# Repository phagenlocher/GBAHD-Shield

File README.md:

# gbaHD Shield
This is a shield for the [gbaHD project](https://github.com/zwenergy/gbaHD).  

This particular fork does change certain parts, but does not add any new features.

#### Features:
- Connects via female headers to the Edge board (shield)
- Has a FFC 40 pin connector for OGBA LCD connector. Need Type-B Cable (Reverse) vvv=======^^^
- Has a FFC 32 pin connector for OGBA LCD connector. Need Type-B Cable (Reverse) vvv=======^^^
- Has a FFC 34 pin connector for GBA-SP LCD connector. Need Type-A Cable (Direct) vvv=======vvv
- Has a FFC 16 pin connector for controls with a wire up board. Need Type-B Cable (Reverse) vvv=======^^^
- Has a ATMEGA328p for using a SNES connector to control the GBA.
- Has a high-side switch for GBA power controls (IGR).
- Has eight (8) testpoints on the bottom side for future features.

## Issues
- no known issues

## Contributing
If you wish to contribute, see something wrong or want to add a feature please make a pull request or leave an issue!

## BOM
|Reference	|Value							|
|---------	|--------						|
|C1, C3		|100nF 0805						|
|C2			|22uF 0805						|
|R1			|2.2K 0805						|
|R2			|1K 0805						|
|R3, R4		|10K 0805						|
|U1			|AMS1117-ADJ SOT223-3			|
|U2,U3		|74HC595 SOIC-16				|
|U4			|SNES 7Pin						|
|U5			|ATMEGA328p-AU					|
|SW1		|Push Button THT 6mm			|
|J2			|JUSHUO AFC07-S32FCC-00			|
|J3			|JUSHUO AFC07-S34FCC-00			|
|J4			|JUSHUO_AFC07-S16FCC-00			|
|J5			|JUSHUO AFC07-S40FCC-00			|
|J6			|PinHeader 1x6 2.54mm			|
|J7, J9		|PinHeader 1x8 2.54mm			|
|J8, J10	|PinHeader 1x10 2.54mm			|
|J11		|PinHeader 2x03 2.54mm			|
|Q1			|SI2301DS P-Chan MOSFET	SOT23	|

## Programming the MCU
In order to program the MCU, you need an arduino to use as ISP.  
Use the following image to wire up an arduino to the board to program it.  
**I would also recomend programming while it's not seated in the FPGA board.**
  
After wiring the board, follow this tutorial to flash the the sketch to the board.  
[ICSP Tutorial](https://www.arduino.cc/en/pmwiki.php?n=Tutorial/ArduinoISP)
As target board choose "Arduino Pro or Pro Mini -  ATmega328p - 8MHz"
Fuses must be Low: 0xE2 High: 0xD9 Ext: 0xFF

## Choosing the supply voltage
As the OGBA and the GBA-SP use different battery technologies, they also require different voltages.
The OGBA needs approx. 3V (2x 1.5V from AA cells - 3.3 will also fit) and the GBA-SP needs 3.3 - 4.2V (Lithium battery - 4.0V will also fit).
Therefore we have a solder-jumper (JP1) which we use to choose between 3.3V and 4.0V.
Plus we need to solder-bridge J1 and J12 due to the fact, that the power-managing chip on the SP mainboard blocks the power on if it detected a
low battery recently. This will replace the power switch which therefore needs to be in **off position always!** 
**v20210406 Owners** If you want to use this board with an SP simply connect the J1 to the VCC-line on the shield and on the mainboard connect EX1 with BAT+ and VCC with VCC.

## Images

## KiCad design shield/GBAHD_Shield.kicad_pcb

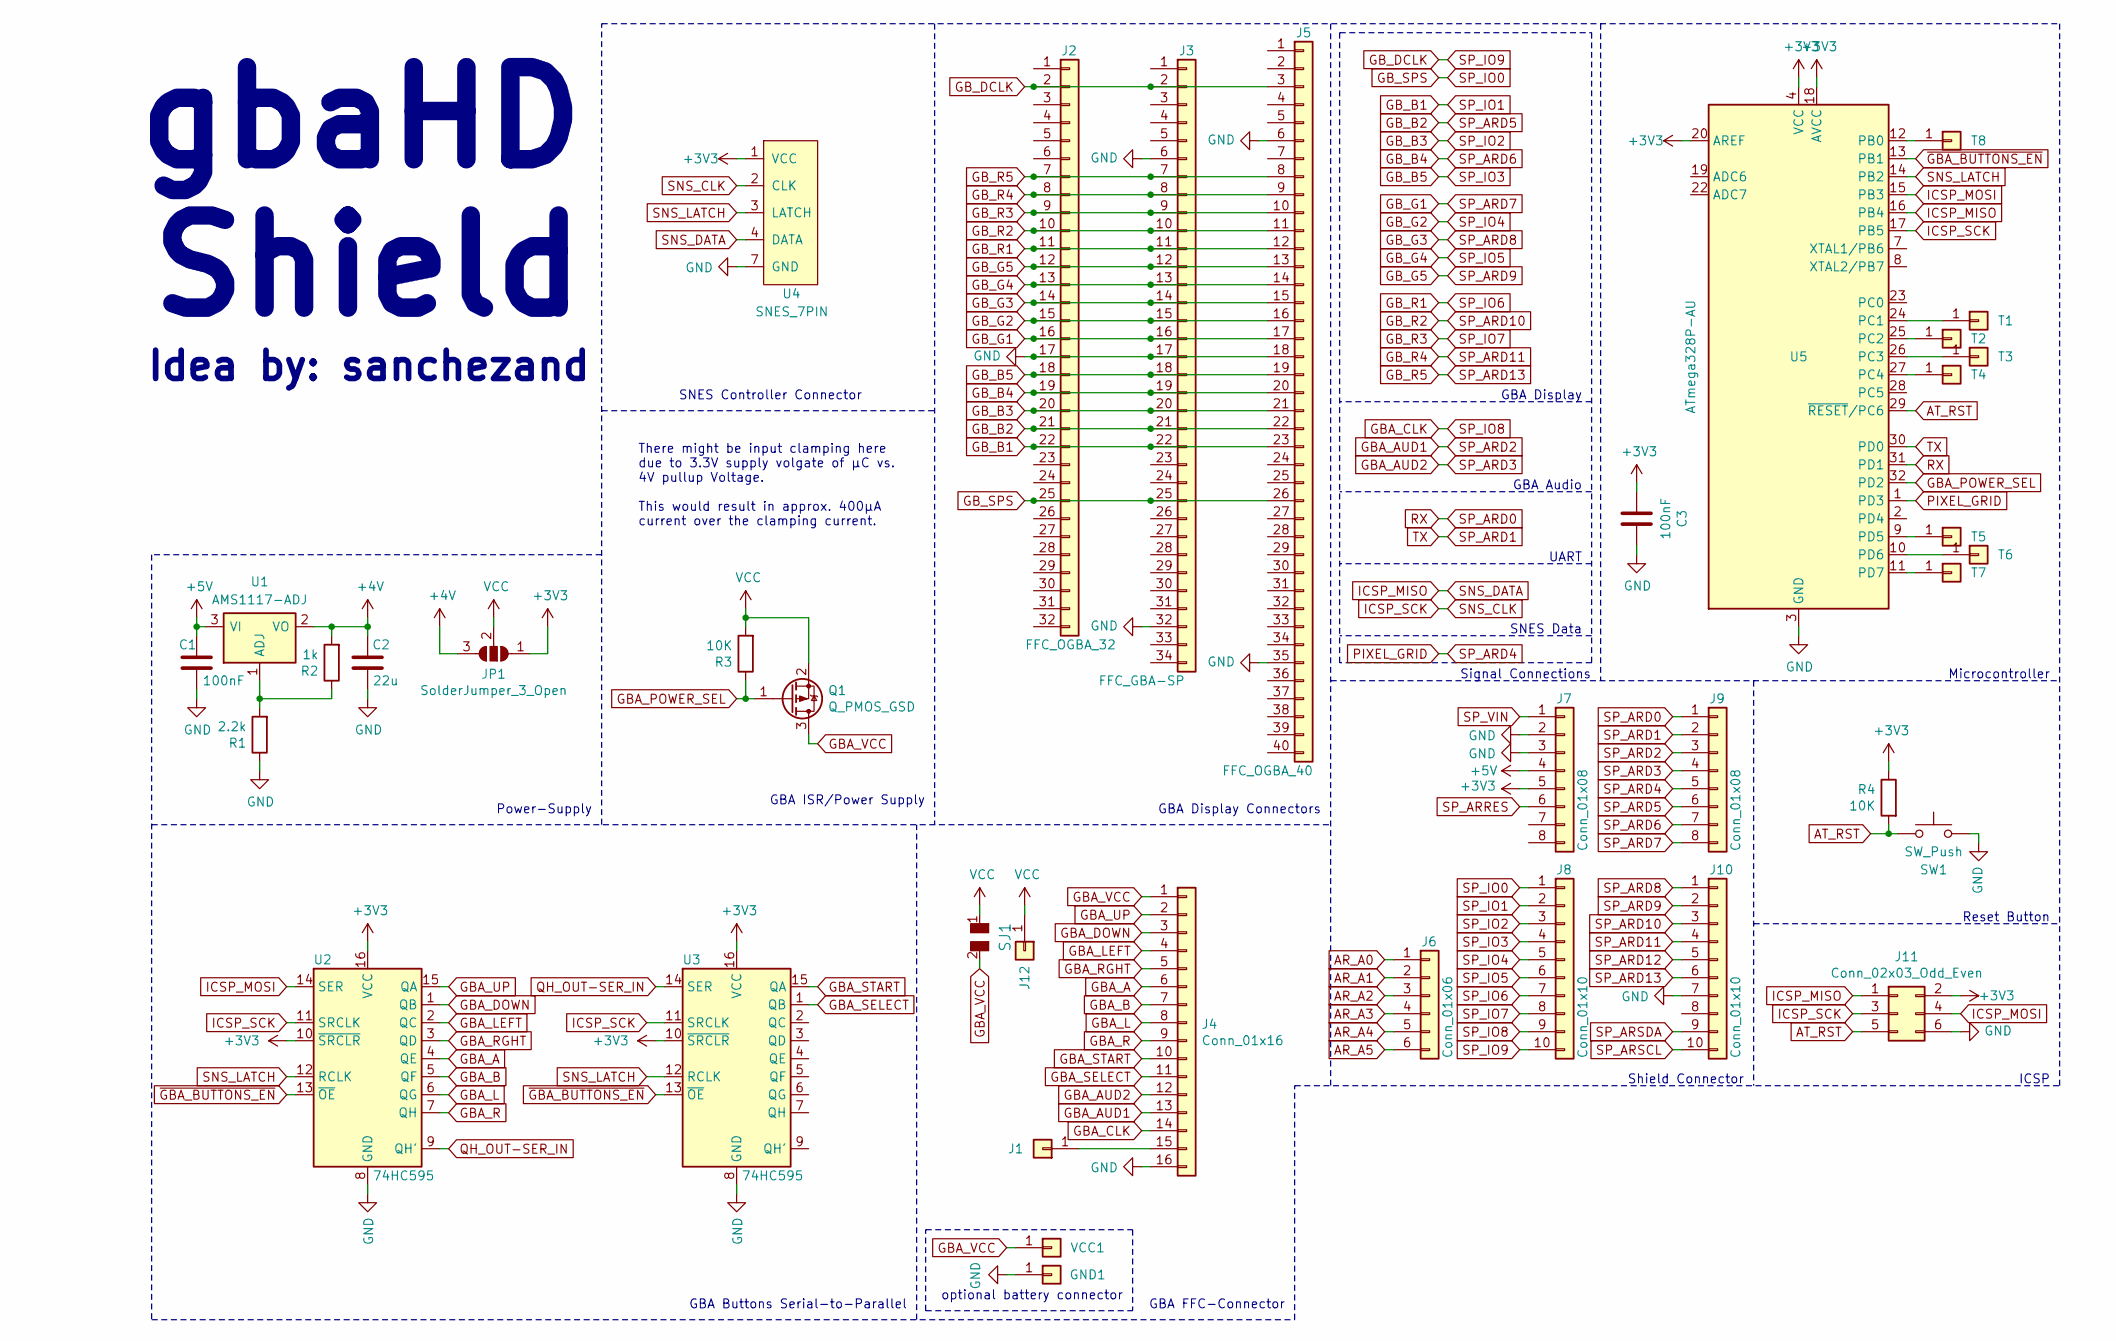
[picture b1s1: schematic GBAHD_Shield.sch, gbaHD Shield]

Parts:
C1, C3: 100nF; C_0805_2012Metric_Pad1.18x1.45mm_HandSolder
C2: 22u; C_0805_2012Metric_Pad1.18x1.45mm_HandSolder
GND1: Conn_01x01; TestPoint_Pad_1.5x1.5mm
J1, J12: Conn_01x01; TestPoint_Pad_1.5x1.5mm
J2: FFC_OGBA_32; TE_3-1734839-2_1x32-1MP_P0.5mm_Horizontal
J3: FFC_GBA-SP; TE_3-1734839-4_1x34-1MP_P0.5mm_Horizontal
J4: Conn_01x16; TE_1-1734839-6_1x16-1MP_P0.5mm_Horizontal
J5: FFC_OGBA_40; TE_4-1734839-0_1x40-1MP_P0.5mm_Horizontal
J6: Conn_01x06; PinHeader_1x06_P2.54mm_Vertical
J7, J9: Conn_01x08; PinHeader_1x08_P2.54mm_Vertical
J8, J10: Conn_01x10; PinHeader_1x10_P2.54mm_Vertical
J11: Conn_02x03_Odd_Even; PinHeader_2x03_P2.54mm_Vertical
JP1: SolderJumper_3_Open; SolderJumper-3_P1.3mm_Open_Pad1.0x1.5mm_NumberLabels
Q1: Q_PMOS_GSD; SOT-23
R1: 2.2k; R_0805_2012Metric_Pad1.20x1.40mm_HandSolder
R2: 1k; R_0805_2012Metric_Pad1.20x1.40mm_HandSolder
R3, R4: 10K; R_0805_2012Metric_Pad1.20x1.40mm_HandSolder
SJ1: SOLDER_JUMPER; SolderJumper-2_P1.3mm_Open_TrianglePad1.0x1.5mm
SW1: SW_Push; SW_PUSH_6mm
T1, T2, T3, T4, T5, T6, T7, T8: Conn_01x01; TestPoint_Pad_1.5x1.5mm
U1: AMS1117-ADJ; SOT-223-3_TabPin2
U2, U3: 74HC595; SOIC-16_3.9x9.9mm_P1.27mm
U4: SNES_7PIN
U5: ATmega328P-AU; TQFP-32_7x7mm_P0.8mm
VCC1: Conn_01x01; TestPoint_Pad_1.5x1.5mm

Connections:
+3V3: C3.2, J7.5, J11.2, JP1.1 (A), R4.1, U2.10 (~SRCLR), U2.16 (VCC), U3.10 (~SRCLR), U3.16 (VCC), U4.1 (VCC), U5.4 (VCC), U5.6 (VCC), U5.18 (AVCC), U5.20 (AREF)
+4V: C2.2, JP1.3 (B), R2.2, U1.2 (VO)
+5V: C1.2, J7.4, U1.3 (VI)
AR_A0: J6.1
AR_A1: J6.2
AR_A2: J6.3
AR_A3: J6.4
AR_A4: J6.5
AR_A5: J6.6
AT_RST: J11.5, R4.2, SW1.1, U5.29 (~RESET~/PC6)
GBA_A: J4.6, U2.4 (QE)
GBA_AUD1: J4.13, J9.3
GBA_AUD2: J4.12, J9.4
GBA_B: J4.7, U2.5 (QF)
GBA_CLK: J4.14, J8.9
GBA_DOWN: J4.3, U2.1 (QB)
GBA_L: J4.8, U2.6 (QG)
GBA_LEFT: J4.4, U2.2 (QC)
GBA_POWER_SEL: Q1.1 (G), R3.1, U5.32 (PD2)
GBA_R: J4.9, U2.7 (QH)
GBA_RGHT: J4.5, U2.3 (QD)
GBA_SELECT: J4.11, U3.1 (QB)
GBA_START: J4.10, U3.15 (QA)
GBA_UP: J4.2, U2.15 (QA)
GBA_VCC: J4.1, Q1.3 (D), SJ1.2, VCC1.1
GB_B1: J2.22, J3.22, J5.23, J8.2
GB_B2: J2.21, J3.21, J5.22, J9.6
GB_B3: J2.20, J3.20, J5.21, J8.3
GB_B4: J2.19, J3.19, J5.20, J9.7
GB_B5: J2.18, J3.18, J5.19, J8.4
GB_DCLK: J2.2, J3.2, J5.3, J8.10
GB_G1: J2.16, J3.16, J5.17, J9.8
GB_G2: J2.15, J3.15, J5.16, J8.5
GB_G3: J2.14, J3.14, J5.15, J10.1
GB_G4: J2.13, J3.13, J5.14, J8.6
GB_G5: J2.12, J3.12, J5.13, J10.2
GB_R1: J2.11, J3.11, J5.12, J8.7
GB_R2: J2.10, J3.10, J5.11, J10.3
GB_R3: J2.9, J3.9, J5.10, J8.8
GB_R4: J2.8, J3.8, J5.9, J10.4
GB_R5: J2.7, J3.7, J5.8, J10.6
GB_SPS: J2.25, J3.25, J5.26, J8.1
GND: C1.1, C2.1, C3.1, GND1.1, J2.17, J3.6, J3.17, J3.32, J4.16, J5.6, J5.18, J5.35, J7.2, J7.3, J10.7, J11.6, R1.1, SW1.2, U2.8 (GND), U3.8 (GND), U4.7 (GND), U5.3 (GND), U5.5 (GND), U5.21 (GND)
ICSP_MISO: J11.1, U4.4 (DATA), U5.16 (PB4)
ICSP_MOSI: J11.4, U2.14 (SER), U5.15 (PB3)
ICSP_SCK: J11.3, U2.11 (SRCLK), U3.11 (SRCLK), U4.2 (CLK), U5.17 (PB5)
unnamed: J1.1, J4.15
unnamed: R1.2, R2.1, U1.1 (ADJ)
unnamed: T1.1, U5.24 (PC1)
unnamed: T2.1, U5.25 (PC2)
unnamed: T3.1, U5.26 (PC3)
unnamed: T4.1, U5.27 (PC4)
unnamed: T5.1, U5.9 (PD5)
unnamed: T6.1, U5.10 (PD6)
unnamed: T7.1, U5.11 (PD7)
unnamed: T8.1, U5.12 (PB0)
PIXEL_GRID: J9.5, U5.1 (PD3)
QH_OUT-SER_IN: U2.9 (QH'), U3.14 (SER)
RX: J9.1, U5.31 (PD1)
SNS_LATCH: U2.12 (RCLK), U3.12 (RCLK), U4.3 (LATCH), U5.14 (PB2)
SP_ARD1: J9.2, U5.30 (PD0)
SP_ARD12: J10.5
SP_ARRES: J7.6
SP_ARSCL: J10.10
SP_ARSDA: J10.9
SP_VIN: J7.1
VCC: J12.1, JP1.2 (C), Q1.2 (S), R3.2, SJ1.1
~GBA_BUTTONS_EN~: U2.13 (~OE), U3.13 (~OE), U5.13 (PB1)

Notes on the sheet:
ICSP
Reset Button
Microcontroller
Shield Connector
Signal Connections
SNES Data
UART
GBA Display
GBA Audio
GBA Display Connectors
GBA FFC-Connector
GBA Buttons Serial-to-Parallel
SNES Controller Connector
GBA ISR/Power Supply
gbaHD Shield
Idea by: sanchezand
Power-Supply
optional battery connector
There might be input clamping here due to 3.3V supply volgate of µC vs. 4V pullup Voltage. This would result in approx. 400µA current over the clamping current.

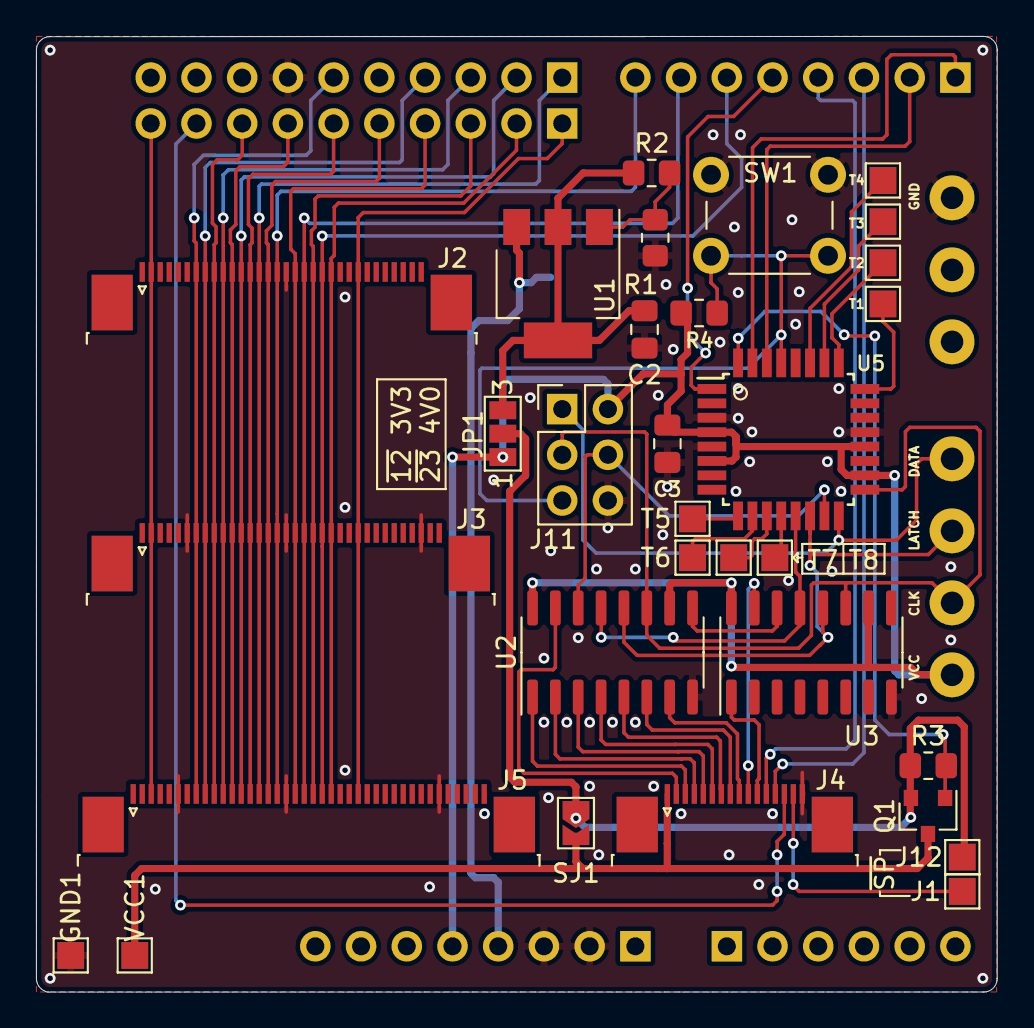
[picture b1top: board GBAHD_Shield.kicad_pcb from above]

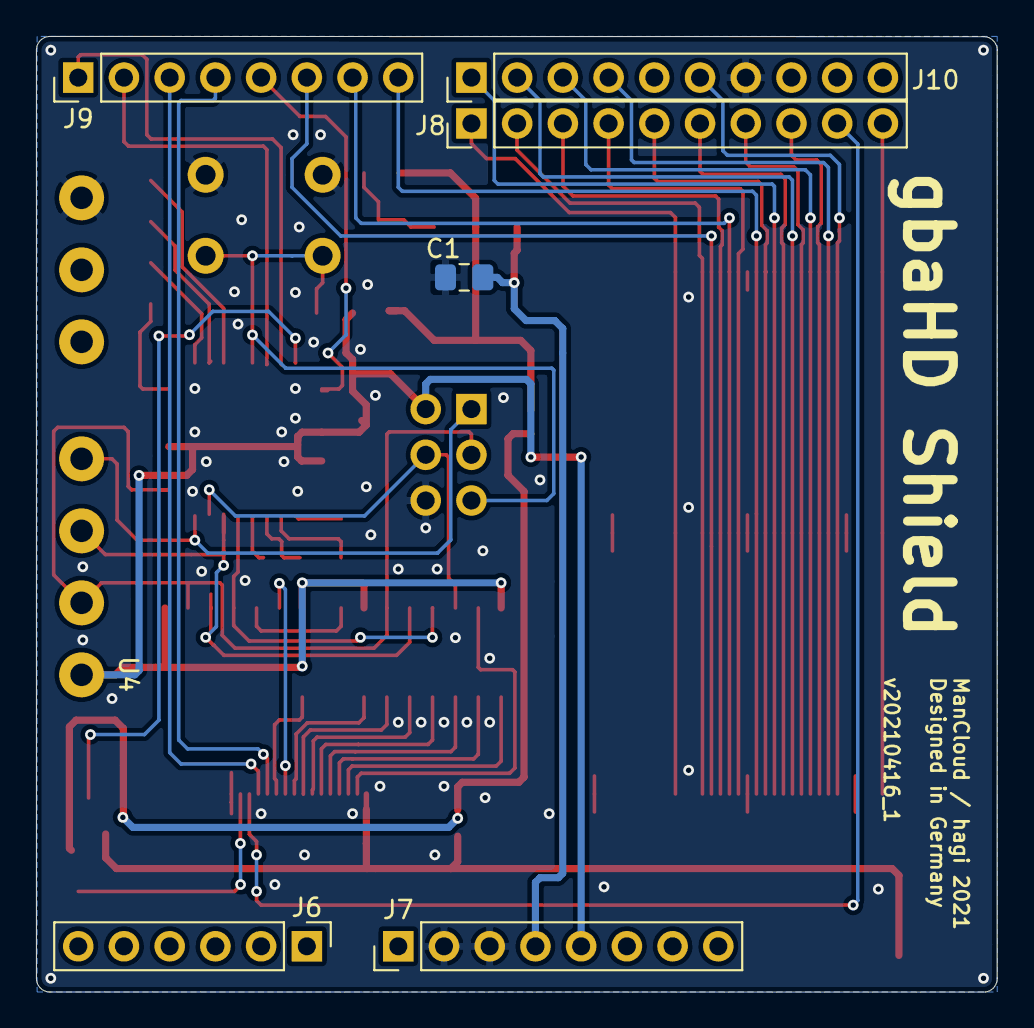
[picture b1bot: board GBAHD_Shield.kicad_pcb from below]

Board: 2 copper layers, 53.4 x 53.1 mm, 38 parts (7 on the bottom side), 57 nets.

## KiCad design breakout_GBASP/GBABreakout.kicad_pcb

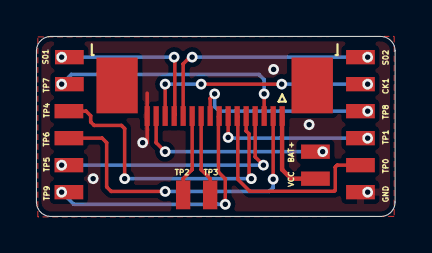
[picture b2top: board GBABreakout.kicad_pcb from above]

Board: 2 copper layers, 19.9 x 10.0 mm, 17 parts (0 on the bottom side), 16 nets.

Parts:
J1: Conn_01x16; TE_1-1734839-6_1x16-1MP_P0.5mm_Horizontal
J2: VCC; SOLDER_PAD
J3: TP6; SOLDER_PAD
J4: TP7; SOLDER_PAD
J5: TP5; SOLDER_PAD
J6: TP4; SOLDER_PAD
J7: TP0; SOLDER_PAD
J8: TP1; SOLDER_PAD
J9: TP9; SOLDER_PAD
J10: TP8; SOLDER_PAD
J11: TP3; SOLDER_PAD
J12: TP2; SOLDER_PAD
J13: S02; SOLDER_PAD
J14: S01; SOLDER_PAD
J15: CK1; SOLDER_PAD
J16: BAT+; SOLDER_PAD
J17: GND; SOLDER_PAD

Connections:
BAT+: J1.15, J16.1
GBA_A: J1.6, J7.1
GBA_AUD1: J1.13, J14.1
GBA_AUD2: J1.12, J13.1
GBA_B: J1.7, J8.1
GBA_CLK: J1.14, J15.1
GBA_DOWN: J1.3, J4.1
GBA_L: J1.8, J9.1
GBA_LEFT: J1.4, J5.1
GBA_R: J1.9, J10.1
GBA_RIGHT: J1.5, J6.1
GBA_SELECT: J1.11, J12.1
GBA_START: J1.10, J11.1
GBA_UP: J1.2, J3.1
GBA_VCC: J1.1, J2.1
GND: J1.16, J17.1

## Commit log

2021-05-22 Switched Voltage Regulator to SOT-223 package and Push Button to THT
2021-05-22 Cleanup for shield pcb
2021-05-22 More readable silkscreen on breakout boards
